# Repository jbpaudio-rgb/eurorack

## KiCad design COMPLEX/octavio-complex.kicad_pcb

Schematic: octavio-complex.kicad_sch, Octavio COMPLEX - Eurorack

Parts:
C1, C2: 10u 25V; C_1206_3216Metric; MPN X5R/X7R 1206
C3, C8: 100p; C_0603_1608Metric
C4, C9: 10n C0G; C_1206_3216Metric; MPN 10 nF C0G/NP0 1206 (condensateur de tim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
C5, C10: 220p; C_0603_1608Metric
C6, C16: 47p; C_0603_1608Metric
C7, C17, C18, C19, C20, C21, C22, C23, C24, C25, C26, C27, C28, C29, C30, C31, C32, C33, C34, C35, C36, C37, C38, C39, C40, C41, C42, C43, C44, C45, C46: 100n; C_0603_1608Metric
C11, C12, C13, C14, C15: 22p; C_0603_1608Metric
C47, C48: 330p; C_0603_1608Metric
D1, D2: SS14; D_SMA; MPN SS14 (40 V 1 A Schottky)
D3, D4, D5, D6, D7, D8, D9, D10, D11, D12, D13, D14, D15, D16, D17, D18, D19, D20: 1N4148W; D_SOD-123; MPN 1N4148W
J1: Eurorack 2x5; IDC-Header_2x05_P2.54mm_Vertical; MPN Shrouded header 2x5 2.54 mm
J2, J9: 1V/OCT; Jack_3.5mm_Thonkiconn_PJ398SM; MPN QingPu WQP-PJ301M-12 (Thonkiconn)
J3, J10: CV; Jack_3.5mm_Thonkiconn_PJ398SM; MPN QingPu WQP-PJ301M-12 (Thonkiconn)
J4, J11: FM; Jack_3.5mm_Thonkiconn_PJ398SM; MPN QingPu WQP-PJ301M-12 (Thonkiconn)
J5: TRI; Jack_3.5mm_Thonkiconn_PJ398SM; MPN QingPu WQP-PJ301M-12 (Thonkiconn)
J6: SIGNAL; Jack_3.5mm_Thonkiconn_PJ398SM; MPN QingPu WQP-PJ301M-12 (Thonkiconn)
J7: INDEX CV; Jack_3.5mm_Thonkiconn_PJ398SM; MPN QingPu WQP-PJ301M-12 (Thonkiconn)
J8: PHASE LOCK; Jack_3.5mm_Thonkiconn_PJ398SM; MPN QingPu WQP-PJ301M-12 (Thonkiconn)
J12: SINE; Jack_3.5mm_Thonkiconn_PJ398SM; MPN QingPu WQP-PJ301M-12 (Thonkiconn)
J13: SQUARE; Jack_3.5mm_Thonkiconn_PJ398SM; MPN QingPu WQP-PJ301M-12 (Thonkiconn)
J14: SYMMETRY CV; Jack_3.5mm_Thonkiconn_PJ398SM; MPN QingPu WQP-PJ301M-12 (Thonkiconn)
J15: TIMBRE CV; Jack_3.5mm_Thonkiconn_PJ398SM; MPN QingPu WQP-PJ301M-12 (Thonkiconn)
J16: ORDER CV; Jack_3.5mm_Thonkiconn_PJ398SM; MPN QingPu WQP-PJ301M-12 (Thonkiconn)
J17: FINAL; Jack_3.5mm_Thonkiconn_PJ398SM; MPN QingPu WQP-PJ301M-12 (Thonkiconn)
Q1, Q3, Q5: BC847DS; SOT-457; MPN BC847DS,115 (Nexperia, paire double)
Q2, Q4: MMBFJ112; SOT-23; MPN MMBFJ112 (JFET N, D-S-G)
R1, R51: 14k; R_0603_1608Metric
R2, R3, R4, R8, R22, R25, R26, R28, R31, R32, R33, R40, R41, R52, R53, R54, R70, R73, R74, R76, R79, R80, R98, R103, R104, R106, R111, R112, R121, R122, R123, R124, R126, R127, R129, R130, R132, R133, R135, R141, R143, R144, R146, R147, R149, R153, R154, R155, R163, R164, R165, R173, R174, R175, R193, R196: 10k; R_0603_1608Metric
R5, R6, R55, R56: 5k36; R_0603_1608Metric
R7: 7k15; R_0603_1608Metric
R9, R10, R12, R14, R15, R16, R36, R37, R38, R39, R49, R57, R58, R60, R62, R63, R95, R96, R97, R101, R102, R109, R110, R119, R120: 100k; R_0603_1608Metric
R11: 100k; R_0603_1608Metric; MPN 100k 0,1 % 25 ppm
R13, R61, R87, R194, R197: 1M; R_0603_1608Metric
R17, R65: 1k TC; R_0603_1608Metric; MPN 1k +3300 ppm/K (thermistance de compens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
R18, R66, R82, R83: 680; R_0603_1608Metric
R19, R67: 549k; R_0603_1608Metric
R20, R34, R35, R68, R92, R93, R192: 1k; R_0603_1608Metric
R21, R50, R69: 22k; R_0603_1608Metric
R23, R27, R71, R75, R99, R105, R136, R150, R183, R185: 20k; R_0603_1608Metric
R24, R72, R107, R145, R148, R184: 48k7; R_0603_1608Metric
R29, R77: 40k2; R_0603_1608Metric
R30, R78: 95k3; R_0603_1608Metric
R42, R47, R48, R81, R85, R86, R113, R156, R161, R162, R166, R171, R172, R176, R181, R182, R186, R191: 47k; R_0603_1608Metric
R43, R44, R114, R115, R157, R158, R167, R168, R177, R178, R187, R188: 100; R_0603_1608Metric
R45, R159, R169, R179: 19k1; R_0603_1608Metric
R46, R160, R170, R180: 2k15; R_0603_1608Metric
R59: 100k; R_0603_1608Metric; MPN 100k 0,1 % 25 ppm (précision 1 V/oct)
R64, R118: 200k; R_0603_1608Metric
R84: 113k; R_0603_1608Metric
R88, R90: 470k; R_0603_1608Metric
R89, R91: 560k; R_0603_1608Metric
R94, R100, R108: 2k; R_0603_1608Metric
R116: 27k; R_0603_1608Metric
R117: 3k; R_0603_1608Metric
R125, R128: 46k4; R_0603_1608Metric
R131, R134: 15k4; R_0603_1608Metric
R137, R138, R139, R140, R151, R152: 4k99; R_0603_1608Metric
R142: 6k98; R_0603_1608Metric
R189: 9k53; R_0603_1608Metric
R190: 1k07; R_0603_1608Metric
R195, R198: 4k7; R_0603_1608Metric
RV1, RV2, RV3, RV4, RV7, RV8, RV9, RV10, RV11, RV12, RV16, RV17, RV18, RV19: 10k B; Pot_Alpha_9mm_Vertical; MPN POT-R09V-10K (9 mm vertical, B10k)
RV5, RV13: 500; Trim_SMD_Bourns_3314J; MPN Bourns 3314J-1-501E (réglage V/OCT)
RV6, RV14: 1k; Trim_SMD_Bourns_3314J; MPN Bourns 3314J-1-102E (réglage HF)
RV15: 1k; Trim_SMD_Bourns_3314J; MPN Bourns 3314J-1-102E (symétrie du sinus)
SW1: AUDIO / LFO; Toggle_SPDT_Dailywell_2MS1; MPN C&K T101MH9ABE (SPDT ON-ON)
SW2: TRI / SQR / SAW; Toggle_SPDT_Dailywell_2MS1; MPN SPDT ON-OFF-ON (ex. C&K T103MH9ABE) : c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
SW3: AMPL ON / OFF; Toggle_SPDT_Dailywell_2MS1; MPN C&K T101MH9ABE (SPDT ON-ON)
SW4: PITCH ON / OFF; Toggle_SPDT_Dailywell_2MS1; MPN C&K T101MH9ABE (SPDT ON-ON)
SW5: TIMBRE ON / OFF; Toggle_SPDT_Dailywell_2MS1; MPN C&K T101MH9ABE (SPDT ON-ON)
U1, U2, U3, U4, U5, U6, U7, U8, U9, U10, U11, U12: TL074; SOIC-14_3.9x8.7mm_P1.27mm; MPN TL074CDR
U13, U14, U15: LM13700; SOIC-16_3.9x9.9mm_P1.27mm; MPN LM13700MX/NOPB

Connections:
+12V: C1.1, C17.1, C19.1, C21.1, C23.1, C25.1, C27.1, C29.1, C31.1, C33.1, C35.1, C37.1, C39.1, C41.1, C43.1, C45.1, D1.1 (K), R1.1, R3.1, R5.1, R19.1, R30.1, R51.1, R53.1, R55.1, R67.1, R78.1, R85.1, R86.1, R94.1, R100.1, R108.1, R128.1, R134.1, R148.1, RV15.3, U1.4 (V+), U2.4 (V+), U3.4 (V+), U4.4 (V+), U5.4 (V+), U6.4 (V+), U7.4 (V+), U8.4 (V+), U9.4 (V+), U10.4 (V+), U11.4 (V+), U12.4 (V+), U13.11 (V+), U14.11 (V+), U15.11 (V+)
+12V_IN: D1.2 (A), J1.9, J1.10
-12V: C2.2, C18.2, C20.2, C22.2, C24.2, C26.2, C28.2, C30.2, C32.2, C34.2, C36.2, C38.2, C40.2, C42.2, C44.2, C46.2, D2.2 (A), R4.2, R6.2, R7.1, R21.2, R24.1, R46.2, R54.2, R56.2, R69.2, R72.1, R84.2, R107.1, R117.2, R125.1, R131.1, R145.1, R160.2, R170.2, R180.2, R184.1, R190.2, RV15.1, U1.11 (V-), U2.11 (V-), U3.11 (V-), U4.11 (V-), U5.11 (V-), U6.11 (V-), U7.11 (V-), U8.11 (V-), U9.11 (V-), U10.11 (V-), U11.11 (V-), U12.11 (V-), U13.6 (V-), U14.6 (V-), U15.6 (V-)
-12V_IN: D2.1 (K), J1.1, J1.2
AMN: R183.2, R184.2, R185.1, U12.6 (-B)
AMV: R185.2, R189.1, U12.7 (OB)
COMA: R183.1, SW3.2 (COM)
COMP: R64.1, SW4.2 (COM)
COMT: R97.1, SW5.2 (COM)
C_CMPP: C48.2, R196.2, R197.2, U5.5 (+B)
C_EN: Q3.1 (E1), Q3.4 (E2), R68.2
C_FB1: R65.2, RV13.1
C_FB2: R66.1, RV13.2 (W), RV13.3
C_GATE: C10.2, Q4.3 (C), R69.1, R198.2
C_GX: C10.1, D20.1 (K), R198.1
C_HFC: C9.2, Q4.1 (B), RV14.1
C_HWA: D5.1 (K), D6.2 (A), U5.14 (OD)
C_HWN: D6.1 (K), R73.2, R74.1, U5.13 (-D)
C_HWO: D5.2 (A), R74.2, R76.1
C_INTN: C9.1, Q3.3 (C2), Q4.2 (E), U5.2 (-A)
C_QRC: C8.2, Q3.6 (C1), R67.2, U4.13 (-D)
C_RAMP: R70.1, R196.1, RV14.2 (W), RV14.3, U5.1 (OA)
C_REF: R50.2, R51.2, R52.1, U5.6 (-B)
C_RSTQ: C48.1, D20.2 (A), R197.1, U5.7 (OB)
C_SAWN: R70.2, R71.1, R72.2, U5.9 (-C)
C_SAWO: R71.2, R73.1, R75.1, R154.1, R161.1, U5.8 (OC), U6.5 (+B)
C_SB1: Q5.2 (B1), R81.2, R82.1
C_SB2: Q5.5 (B2), R83.1, R87.2
C_SC1: Q5.6 (C1), R85.2, R88.1
C_SC2: Q5.3 (C2), R86.2, R90.1
C_SE: Q5.1 (E1), Q5.4 (E2), R84.1
C_SINN: R88.2, R89.1, U6.9 (-C)
C_SINO: R89.2, R92.1, R113.1, R118.1, R141.1, R164.1, R171.1, U6.8 (OC)
C_SINP: R90.2, R91.1, U6.10 (+C)
C_SINT: R87.1, RV15.2 (W)
C_SN: R59.2, R60.2, R61.2, R62.2, R63.2, R64.2, R65.1, U4.9 (-C)
C_SQC: R79.1, U6.7 (OB)
C_SQO: R79.2, R80.1, U6.12 (+D)
C_TRIO: R77.2, R81.1, U6.1 (OA)
C_TRN: R75.2, R76.2, R77.1, R78.2, U6.2 (-A)
C_VD: C8.1, R68.1, U4.14 (OD)
C_VREFB: Q3.2 (B1), R66.2, U4.8 (OC)
FINALJ: J17.T, R192.2
FINALO: C16.2, R191.2, R192.1, U12.8 (OC)
FOLDO: C12.2, R136.2, R174.1, R181.1, U9.8 (OC)
FS: C12.1, R135.2, R136.1, R137.2, R138.2, R139.2, R140.2, U9.9 (-C)
GND: C1.2, C2.1, C17.2, C18.1, C19.2, C20.1, C21.2, C22.1, C23.2, C24.1, C25.2, C26.1, C27.2, C28.1, C29.2, C30.1, C31.2, C32.1, C33.2, C34.1, C35.2, C36.1, C37.2, C38.1, C39.2, C40.1, C41.2, C42.1, C43.2, C44.1, C45.2, C46.1, J1.3, J1.4, J1.5, J1.6, J1.7, J1.8, J2.S, J2.TN, J3.S, J3.TN, J4.S, J4.TN, J5.S, J6.S, J7.S, J7.TN, J8.S, J8.TN, J9.S, J9.TN, J10.S, J10.TN, J11.S, J11.TN, J12.S, J13.S, J14.S, J14.TN, J15.S, J15.TN, J16.S, J16.TN, J17.S, Q1.5 (B2), Q3.5 (B2), R2.2, R8.2, R32.2, R39.2, R40.2, R43.2, R44.2, R49.2, R52.2, R80.2, R82.2, R83.2, R91.2, R98.2, R103.2, R111.2, R114.2, R115.2, R157.2, R158.2, R167.2, R168.2, R177.2, R178.2, R187.2, R188.2, RV4.1 (CCW), RV8.1 (CCW), RV12.1 (CCW), RV16.1 (CCW), RV17.1 (CCW), RV18.1 (CCW), RV19.1 (CCW), SW1.1, SW3.3, SW4.3, SW5.3, U1.3 (+A), U1.5 (+B), U1.10 (+C), U1.12 (+D), U2.5 (+B), U2.10 (+C), U2.12 (+D), U3.2 (-A), U3.10 (+C), U4.3 (+A), U4.5 (+B), U4.10 (+C), U4.12 (+D), U5.3 (+A), U5.10 (+C), U5.12 (+D), U6.3 (+A), U6.6 (-B), U7.10 (+C), U8.3 (+A), U8.5 (+B), U8.10 (+C), U8.12 (+D), U9.3 (+A), U9.5 (+B), U9.10 (+C), U9.12 (+D), U10.3 (+A), U10.5 (+B), U10.10 (+C), U10.12 (+D), U11.3 (+A), U11.5 (+B), U11.10 (+C), U11.12 (+D), U12.3 (+A), U12.5 (+B), U12.10 (+C), U12.12 (+D)
IXCN: R40.1, R41.2, U3.13 (-D)
IXCP: R38.2, R39.1, U3.12 (+D)
IXCV: R41.1, R45.1, U3.14 (OD)
IXCVJ: J7.T, R38.1
IX_W: R47.1, RV7.2 (W)
LFOREF: R7.2, R8.1, SW1.3
MCVIN: R9.2, R10.1, U1.2 (-A)
MCVINV: R10.2, RV3.1 (CCW), U1.1 (OA)
MCVJ: J3.T, R9.1, RV3.3 (CW)
MCV_W: R14.1, RV3.2 (W)
MFB: R6.1, RV2.1 (CCW)
MFMJ: J4.T, RV4.3 (CW)
MFM_W: R15.1, RV4.2 (W)
MFN_W: R13.1, RV2.2 (W)
MFT: R5.2, RV2.3 (CW)
MF_W: R12.1, RV1.2 (W)
MIN: C6.2, R48.2, SW3.1, SW4.1, SW5.1, U4.1 (OA)
MISUM: C6.1, R47.2, R48.1, U4.2 (-A), U13.5 (OUT1)
MKB: R4.1, RV1.1 (CCW)
MKT: R3.2, RV1.3 (CW)
MO: R150.2, R153.1, U10.8 (OC)
MODW: R34.1, R36.1, R42.1, RV7.3 (CW), U3.6 (-B), U3.7 (OB)
MS: R149.2, R150.1, R151.2, R152.2, U10.9 (-C)
MSIGJ: J6.T, R34.2
MTRIJ: J5.T, R35.2
MVOJ: J2.T, R11.1
MWIIN: R36.2, R37.1, U3.9 (-C)
MWIINV: R37.2, RV7.1 (CCW), U3.8 (OC)
MWSEL: R33.2, SW2.2 (COM), U3.5 (+B)
M_CMPP: C47.2, R193.2, R194.2, U2.3 (+A)
M_EN: Q1.1 (E1), Q1.4 (E2), R20.2
M_FB1: R17.2, RV5.1
M_FB2: R18.1, RV5.2 (W), RV5.3
M_GATE: C5.2, Q2.3 (C), R21.1, R195.2
M_GX: C5.1, D19.1 (K), R195.1
M_HFC: C4.2, Q2.1 (B), RV6.1
M_HWA: D3.1 (K), D4.2 (A), U2.8 (OC)
M_HWN: D4.1 (K), R25.2, R26.1, U2.9 (-C)
M_HWO: D3.2 (A), R26.2, R28.1
M_INTN: C4.1, Q1.3 (C2), Q2.2 (E), U1.13 (-D)
M_QRC: C3.2, Q1.6 (C1), R19.2, U1.9 (-C)
M_RAMP: R22.1, R193.1, RV6.2 (W), RV6.3, U1.14 (OD)
M_RSTQ: C47.1, D19.2 (A), R194.1, U2.1 (OA)
M_SAWN: R22.2, R23.1, R24.2, U2.6 (-B)
M_SAWO: R23.2, R25.1, R27.1, SW2.3, U2.7 (OB), U3.3 (+A)
M_SN: R11.2, R12.2, R13.2, R14.2, R15.2, R16.2, R17.1, U1.6 (-B)
M_SQC: R31.1, U3.1 (OA)
M_SQO: R31.2, R32.1, R33.1
M_TRIO: R29.2, R35.1, SW2.1, U2.14 (OD)
M_TRN: R27.2, R28.2, R29.1, R30.2, U2.13 (-D)
M_VD: C3.1, R20.1, U1.8 (OC)
M_VREFB: Q1.2 (B1), R18.2, U1.7 (OB)
O00I: R45.2, R46.1, U13.1 (IABC1)
O00N: R44.1, U13.4 (-IN1)
O00P: R42.2, R43.1, U13.3 (+IN1)
O01I: R116.2, R117.1, U13.16 (IABC2)
O01N: R115.1, U13.13 (-IN2)
O01P: R113.2, R114.1, U13.14 (+IN2)
O10I: R159.2, R160.1, U14.1 (IABC1)
O10N: R158.1, U14.4 (-IN1)
O10P: R156.2, R157.1, U14.3 (+IN1)
O11I: R169.2, R170.1, U14.16 (IABC2)
O11N: R168.1, U14.13 (-IN2)
O11P: R166.2, R167.1, U14.14 (+IN2)
O20I: R179.2, R180.1, U15.1 (IABC1)
O20N: R178.1, U15.4 (-IN1)
O20P: R176.2, R177.1, U15.3 (+IN1)
O21I: R189.2, R190.1, U15.16 (IABC2)
O21N: R188.1, U15.13 (-IN2)
O21P: R186.2, R187.1, U15.14 (+IN2)
ORCVJ: J16.T, R110.1
ORT: R108.2, RV19.3 (CW)
ORV: R112.1, R179.1, U7.14 (OD)
ORV_N: R111.1, R112.2, U7.13 (-D)
ORV_P: R109.2, R110.2, U7.12 (+D)
OR_W: R109.1, RV19.2 (W)
OSUM: C16.1, R191.1, U12.9 (-C), U15.12 (OUT2)
PCVIN: R57.2, R58.1, U4.6 (-B)
PCVINV: R58.2, RV11.1 (CCW), U4.7 (OB)
PCVJ: J10.T, R57.1, RV11.3 (CW)
PCV_W: R62.1, RV11.2 (W)
PFB: R56.1, RV10.1 (CCW)
PFMJ: J11.T, RV12.3 (CW)
PFM_W: R63.1, RV12.2 (W)
PFN_W: R61.1, RV10.2 (W)
PFT: R55.2, RV10.3 (CW)
PF_W: R60.1, RV9.2 (W)
PKB: R54.1, RV9.1 (CCW)
PKT: R53.2, RV9.3 (CW)
PLAC: C7.2, R49.1, RV8.3 (CW)
PLJ: C7.1, J8.T
PL_W: R50.1, RV8.2 (W)
PVOJ: J9.T, R59.1
REF5: R1.2, R2.1, U2.2 (-A)
RNGS: R16.1, SW1.2 (COM)
SDN: R105.2, R106.1, R107.2, U7.9 (-C)
SINEJ: J12.T, R92.2
SQB: R93.1, U6.13 (-D), U6.14 (OD)
SQJ: J13.T, R93.2
SYCVJ: J14.T, R102.1
SYDC: R106.2, R119.1, U7.8 (OC)
SYT: R100.2, RV18.3 (CW)
SYV: R104.1, R105.1, R159.1, U7.7 (OB)
SYV_N: R103.1, R104.2, U7.6 (-B)
SYV_P: R101.2, R102.2, U7.5 (+B)
SY_W: R101.1, RV18.2 (W)
TBN: R98.1, R99.2, U7.2 (-A)
TBP: R95.2, R96.2, R97.2, U7.3 (+A)
TBT: R94.2, RV16.3 (CW)
TBV: R99.1, R116.1, R169.1, U7.1 (OA)
TB_W: R95.1, RV16.2 (W)
TCVJ: J15.T, RV17.3 (CW)
TCV_W: R96.1, RV17.2 (W)
UNUSED113: U12.13 (-D), U12.14 (OD)
X: C11.2, R120.2, R121.1, R123.1, R126.1, R135.1, U8.1 (OA)
XIN: R121.2, R122.1, U8.6 (-B)
XM: R142.2, R143.1, R146.1, R149.1, U9.14 (OD)
XMN: R141.2, R142.1, U9.13 (-D)
XN: R122.2, R129.1, R132.1, U8.7 (OB)
XS: C13.2, R162.2, R163.1, U11.1 (OA)
XSUM: C11.1, R118.2, R119.2, R120.1, U8.2 (-A), U13.12 (OUT2)
XS_D: R155.2, R156.1, U10.14 (OD)
XS_DN: R153.2, R154.2, R155.1, U10.13 (-D)
XS_S: C13.1, R161.2, R162.1, U11.2 (-A), U14.5 (OUT1)
Y1N: D10.1 (K), R127.1, R138.1
Y1N_N: D9.2 (A), R126.2, R127.2, R128.2, U8.13 (-D)
Y1N_O: D9.1 (K), D10.2 (A), U8.14 (OD)
Y1P: D8.2 (A), R124.1, R137.1
Y1P_N: D7.1 (K), R123.2, R124.2, R125.2, U8.9 (-C)
Y1P_O: D7.2 (A), D8.1 (K), U8.8 (OC)
Y2N: D14.1 (K), R133.1, R140.1
Y2N_N: D13.2 (A), R132.2, R133.2, R134.2, U9.6 (-B)
Y2N_O: D13.1 (K), D14.2 (A), U9.7 (OB)
Y2P: D12.2 (A), R130.1, R139.1
Y2P_N: D11.1 (K), R129.2, R130.2, R131.2, U9.2 (-A)
Y2P_O: D11.2 (A), D12.1 (K), U9.1 (OA)
YMN: D18.1 (K), R147.1, R152.1
YMN_N: D17.2 (A), R146.2, R147.2, R148.2, U10.6 (-B)
YMN_O: D17.1 (K), D18.2 (A), U10.7 (OB)
YMP: D16.2 (A), R144.1, R151.1
YMP_N: D15.1 (K), R143.2, R144.2, R145.2, U10.2 (-A)
YMP_O: D15.2 (A), D16.1 (K), U10.1 (OA)
YS: C14.2, R172.2, R173.1, U11.8 (OC)
YS_D: R165.2, R166.1, U11.7 (OB)
YS_DN: R163.2, R164.2, R165.1, U11.6 (-B)
YS_S: C14.1, R171.2, R172.1, U11.9 (-C), U14.12 (OUT2)
ZS: C15.2, R182.2, R186.1, U12.1 (OA)
ZS_D: R175.2, R176.1, U11.14 (OD)
ZS_DN: R173.2, R174.2, R175.1, U11.13 (-D)
ZS_S: C15.1, R181.2, R182.1, U12.2 (-A), U15.5 (OUT1)

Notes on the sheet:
POWER (Eurorack 10 pins)
MOD OSC : FREQ, FINE, RANGE, CV, FM
MODULATION OSC CORE (expo, saw, triangle, square)
MOD OSC : WAVE, OUTPUTS
MOD INDEX (attenuverter + CV OTA), AMPL / PITCH / TIMBRE
PHASE LOCK
PRINCIPAL OSC : FREQ, FINE, CV, FM
COMPLEX OSC CORE (expo, saw, triangle, square)
SINE SHAPER, SINE / SQUARE OUTPUTS
HARMONICS : TIMBRE / SYMMETRY / ORDER controls
HARMONICS : WAVE FOLDER (TIMBRE drive, SYMMETRY DC)
HARMONICS : M SHAPER
HARMONICS : SYMMETRY / TIMBRE / ORDER CROSSFADES
AM + FINAL OUTPUT
JACKS
ICs + DECOUPLING
NOTES
- Architecture inspiree du Buchla 259 (circuit original Octavio) : osc. de modulation, section MOD, osc. principal, HARMONICS.
- Deux coeurs dent de scie facon 921 ; 0 V = 440 Hz (R 549k) ; FREQUENCY +/-4 V = 8 octaves (27 Hz a 7 kHz), FINE +/- une quinte, LFO = -7 octaves.
- MOD INDEX : attenuverter sur le signal de modulation + OTA pour INDEX CV ; AMPL / PITCH / TIMBRE (haut = ON) envoient MIN vers l'AM, le convertisseur expo (200k) et la commande de timbre.
- PHASE LOCK : entree couplee en alternatif injectee dans la reference de remise a zero du coeur principal (verrouillage par injection).
- HARMONICS : replieur (OTA x1..x4 + seuils 2,6 V / 7,8 V, DC de SYMMETRY), forme M (repli doux a 2,5 V), dent de scie du coeur.
- X = SAW -> M (SYMMETRY), Y = SINE -> X (TIMBRE), FINAL = REPLIE -> Y (ORDER), puis AM (OTA).
- -12V = bande rouge du cable.

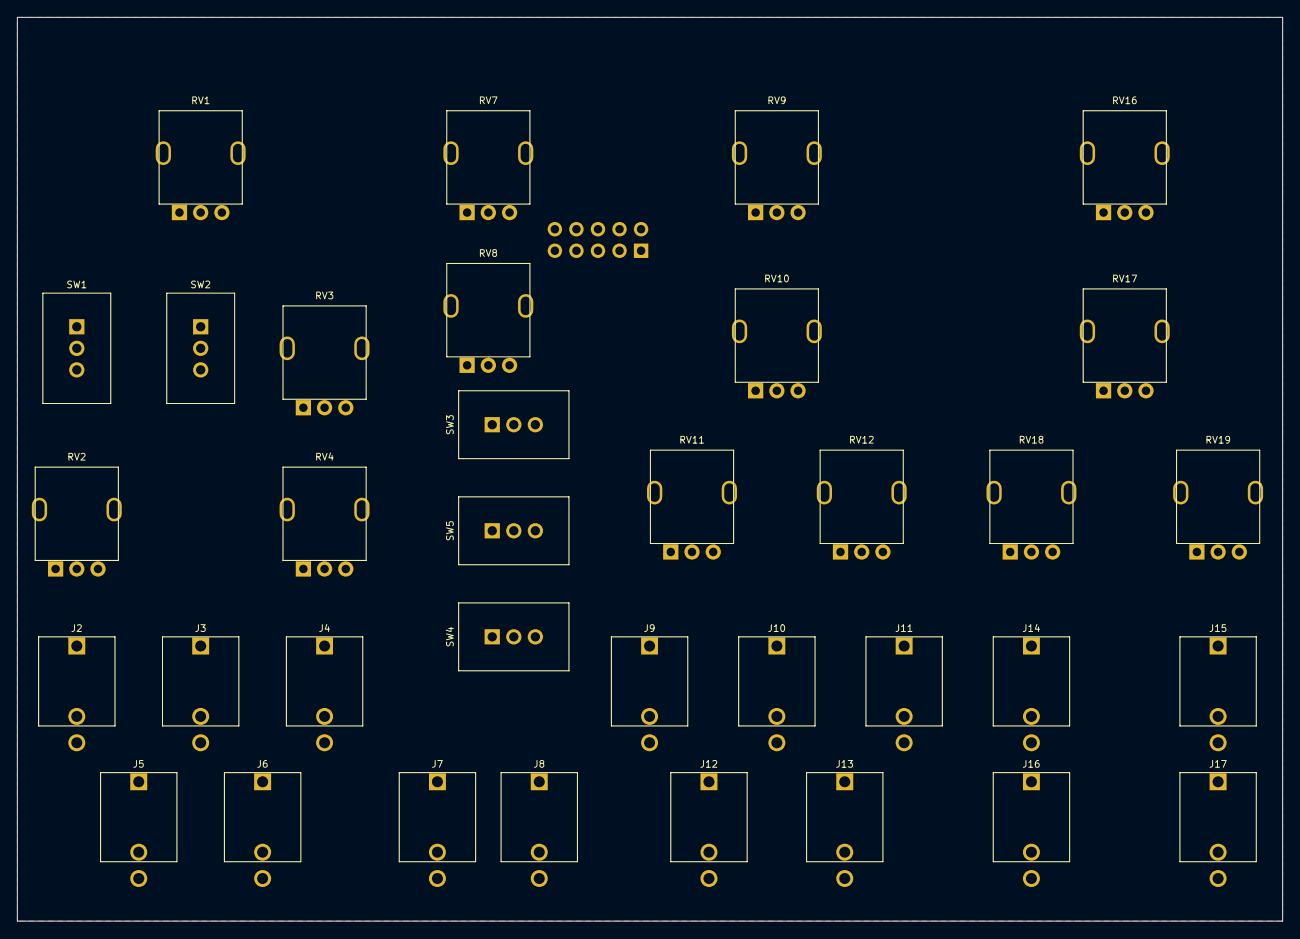
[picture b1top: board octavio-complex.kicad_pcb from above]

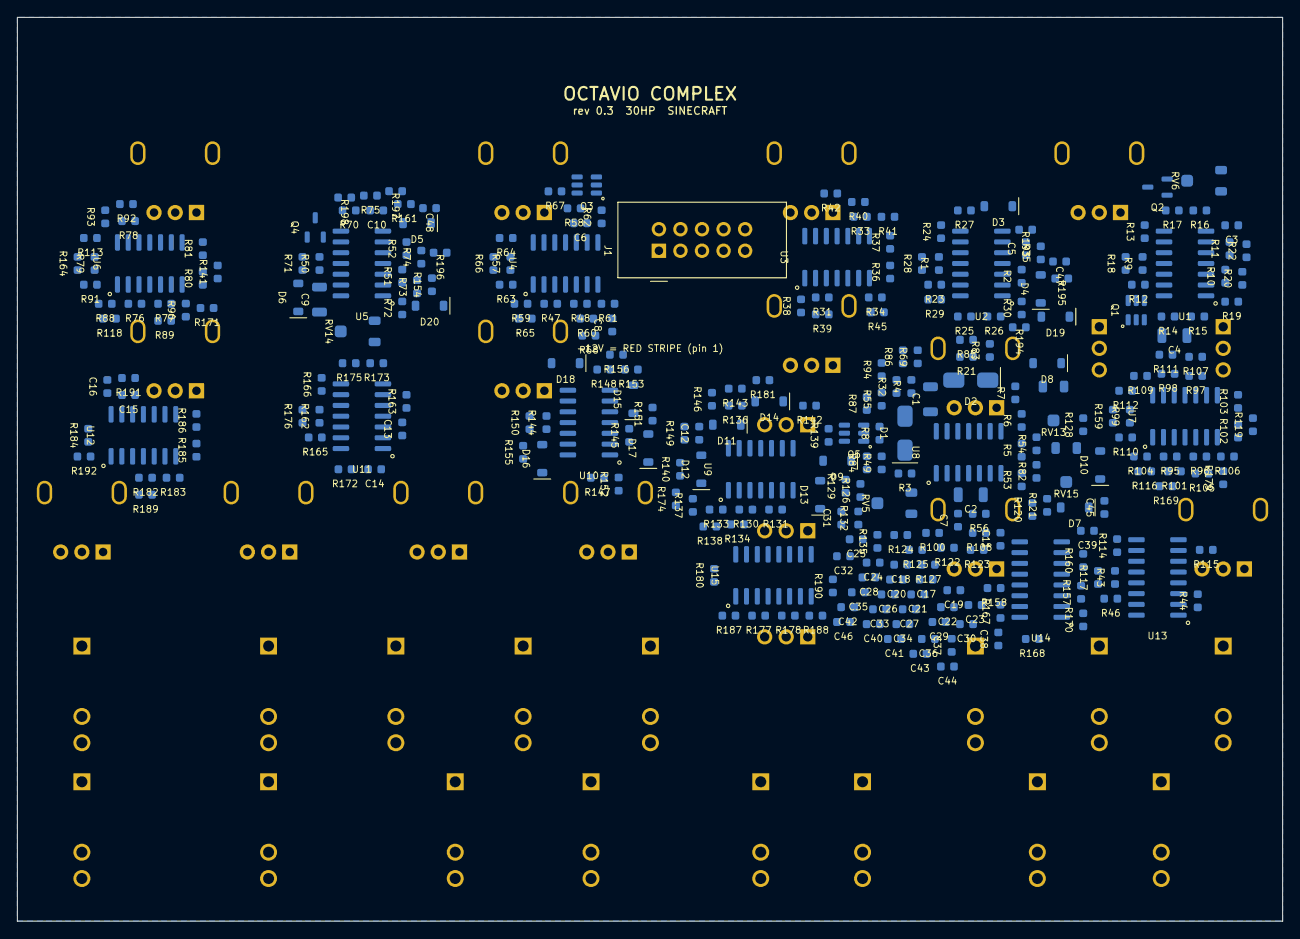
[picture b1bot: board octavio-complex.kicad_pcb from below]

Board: 2 copper layers, 149.1 x 106.5 mm, 327 parts (292 on the bottom side), 197 nets, no tracks yet.

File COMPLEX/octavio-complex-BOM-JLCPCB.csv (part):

Comment,Designator,Footprint,LCSC Part #,Notes
10u 25V X5R/X7R 1206,"C1,C2",C_1206_3216Metric,,X5R/X7R 1206 - SMT bottom - laisser JLC choisir (Basic de preference)
22p,"C11,C12,C13,C14,C15",C_0603_1608Metric,,SMT bottom - laisser JLC choisir (Basic de preference)
100p,"C3,C8",C_0603_1608Metric,,SMT bottom - laisser JLC choisir (Basic de preference)
10n C0G 10 nF C0G/NP0 1206,"C4,C9",C_1206_3216Metric,,10 nF C0G/NP0 1206 (condensateur de timing) - SMT bottom - laisser JLC choisir (Basic de preference)
220p,"C5,C10",C_0603_1608Metric,,SMT bottom - laisser JLC choisir (Basic de preference)
47p,"C6,C16",C_0603_1608Metric,,SMT bottom - laisser JLC choisir (Basic de preference)
100n,"C7,C17,C18,C19,C20,C21,C22,C23,C24,C25,C26,C27,C28,C29,C30,C31,C32,C33,C34,C35,C36,C37,C38,C39,C40,C41,C42,C43,C44,C45,C46",C_0603_1608Metric,,SMT bottom - laisser JLC choisir (Basic de preference)
SS14,"D1,D2",D_SMA,,SS14 (40 V 1 A Schottky) - SMT bottom - laisser JLC choisir (Basic de preference)
1N4148W,"D3,D4,D5,D6,D7,D8,D9,D10,D11,D12,D13,D14,D15,D16,D17,D18,D19,D20",D_SOD-123,,1N4148W - SMT bottom - laisser JLC choisir (Basic de preference)
Eurorack 2x5,J1,IDC-Header_2x05_P2.54mm_Vertical,,Shrouded header 2x5 2.54 mm - THT (wave soldering) - laisser JLC choisir (Basic de preference)
SINE,J12,Jack_3.5mm_Thonkiconn_PJ398SM,C9900080080,QingPu WQP-PJ301M-12 (Thonkiconn) - THT (wave soldering)
SQUARE,J13,Jack_3.5mm_Thonkiconn_PJ398SM,C9900080080,QingPu WQP-PJ301M-12 (Thonkiconn) - THT (wave soldering)
SYMMETRY CV,J14,Jack_3.5mm_Thonkiconn_PJ398SM,C9900080080,QingPu WQP-PJ301M-12 (Thonkiconn) - THT (wave soldering)
TIMBRE CV,J15,Jack_3.5mm_Thonkiconn_PJ398SM,C9900080080,QingPu WQP-PJ301M-12 (Thonkiconn) - THT (wave soldering)
ORDER CV,J16,Jack_3.5mm_Thonkiconn_PJ398SM,C9900080080,QingPu WQP-PJ301M-12 (Thonkiconn) - THT (wave soldering)
FINAL,J17,Jack_3.5mm_Thonkiconn_PJ398SM,C9900080080,QingPu WQP-PJ301M-12 (Thonkiconn) - THT (wave soldering)
1V/OCT,"J2,J9",Jack_3.5mm_Thonkiconn_PJ398SM,C9900080080,QingPu WQP-PJ301M-12 (Thonkiconn) - THT (wave soldering)
CV,"J3,J10",Jack_3.5mm_Thonkiconn_PJ398SM,C9900080080,QingPu WQP-PJ301M-12 (Thonkiconn) - THT (wave soldering)
FM,"J4,J11",Jack_3.5mm_Thonkiconn_PJ398SM,C9900080080,QingPu WQP-PJ301M-12 (Thonkiconn) - THT (wave soldering)
TRI,J5,Jack_3.5mm_Thonkiconn_PJ398SM,C9900080080,QingPu WQP-PJ301M-12 (Thonkiconn) - THT (wave soldering)
SIGNAL,J6,Jack_3.5mm_Thonkiconn_PJ398SM,C9900080080,QingPu WQP-PJ301M-12 (Thonkiconn) - THT (wave soldering)
INDEX CV,J7,Jack_3.5mm_Thonkiconn_PJ398SM,C9900080080,QingPu WQP-PJ301M-12 (Thonkiconn) - THT (wave soldering)
PHASE LOCK,J8,Jack_3.5mm_Thonkiconn_PJ398SM,C9900080080,QingPu WQP-PJ301M-12 (Thonkiconn) - THT (wave soldering)
"BC847DS,115","Q1,Q3,Q5",SOT-457,C549489,"BC847DS,115 (Nexperia, paire double) - SMT bottom"
MMBFJ112,"Q2,Q4",SOT-23,,"MMBFJ112 (JFET N, D-S-G) - SMT bottom - laisser JLC choisir (Basic de preference)"
14k 1% 0805,"R1,R51",R_0603_1608Metric,,SMT bottom - laisser JLC choisir (Basic de preference)
100k 1% 0805,R11,R_0603_1608Metric,,"100k 0,1 % 25 ppm - SMT bottom - laisser JLC choisir (Basic de preference)"
27k 1% 0805,R116,R_0603_1608Metric,,SMT bottom - laisser JLC choisir (Basic de preference)
3k 1% 0805,R117,R_0603_1608Metric,,SMT bottom - laisser JLC choisir (Basic de preference)
46k4 1% 0805,"R125,R128",R_0603_1608Metric,,SMT bottom - laisser JLC choisir (Basic de preference)
1M 1% 0805,"R13,R61,R87,R194,R197",R_0603_1608Metric,,SMT bottom - laisser JLC choisir (Basic de preference)
15k4 1% 0805,"R131,R134",R_0603_1608Metric,,SMT bottom - laisser JLC choisir (Basic de preference)
4k99 1% 0805,"R137,R138,R139,R140,R151,R152",R_0603_1608Metric,,SMT bottom - laisser JLC choisir (Basic de preference)
6k98 1% 0805,R142,R_0603_1608Metric,,SMT bottom - laisser JLC choisir (Basic de preference)
1k TC 1% 0805,"R17,R65",R_0603_1608Metric,,"1k +3300 ppm/K (thermistance de compensation, collée à la paire) - SMT bottom - laisser JLC choisir (Basic de preference)"
680 1% 0805,"R18,R66,R82,R83",R_0603_1608Metric,,SMT bottom - laisser JLC choisir (Basic de preference)
9k53 1% 0805,R189,R_0603_1608Metric,,SMT bottom - laisser JLC choisir (Basic de preference)
549k 1% 0805,"R19,R67",R_0603_1608Metric,,SMT bottom - laisser JLC choisir (Basic de preference)
1k07 1% 0805,R190,R_0603_1608Metric,,SMT bottom - laisser JLC choisir (Basic de preference)
10k 1% 0805,"R2,R3,R4,R8,R22,R25,R26,R28,R31,R32,R33,R40,R41,R52,R53,R54,R70,R73,R74,R76,R79,R80,R98,R103,R104,R106,R111,R112,R121,R122,R123,R124,R126,R127,R129,R130,R132,R133,R135,R141,R143,R144,R146,R147,R149,R153,R154,R155,R163,R164,R165,R173,R174,R175,R193,R196",R_0603_1608Metric,,SMT bottom - laisser JLC choisir (Basic de preference)
1k 1% 0805,"R20,R34,R35,R68,R92,R93,R192",R_0603_1608Metric,,SMT bottom - laisser JLC choisir (Basic de preference)
22k 1% 0805,"R21,R50,R69",R_0603_1608Metric,,SMT bottom - laisser JLC choisir (Basic de preference)
20k 1% 0805,"R23,R27,R71,R75,R99,R105,R136,R150,R183,R185",R_0603_1608Metric,,SMT bottom - laisser JLC choisir (Basic de preference)
48k7 1% 0805,"R24,R72,R107,R145,R148,R184",R_0603_1608Metric,,SMT bottom - laisser JLC choisir (Basic de preference)
40k2 1% 0805,"R29,R77",R_0603_1608Metric,,SMT bottom - laisser JLC choisir (Basic de preference)
95k3 1% 0805,"R30,R78",R_0603_1608Metric,,SMT bottom - laisser JLC choisir (Basic de preference)
47k 1% 0805,"R42,R47,R48,R81,R85,R86,R113,R156,R161,R162,R166,R171,R172,R176,R181,R182,R186,R191",R_0603_1608Metric,,SMT bottom - laisser JLC choisir (Basic de preference)
100 1% 0805,"R43,R44,R114,R115,R157,R158,R167,R168,R177,R178,R187,R188",R_0603_1608Metric,,SMT bottom - laisser JLC choisir (Basic de preference)
19k1 1% 0805,"R45,R159,R169,R179",R_0603_1608Metric,,SMT bottom - laisser JLC choisir (Basic de preference)
2k15 1% 0805,"R46,R160,R170,R180",R_0603_1608Metric,,SMT bottom - laisser JLC choisir (Basic de preference)
5k36 1% 0805,"R5,R6,R55,R56",R_0603_1608Metric,,SMT bottom - laisser JLC choisir (Basic de preference)
100k 1% 0805,R59,R_0603_1608Metric,,"100k 0,1 % 25 ppm (précision 1 V/oct) - SMT bottom - laisser JLC choisir (Basic de preference)"
200k 1% 0805,"R64,R118",R_0603_1608Metric,,SMT bottom - laisser JLC choisir (Basic de preference)
7k15 1% 0805,R7,R_0603_1608Metric,,SMT bottom - laisser JLC choisir (Basic de preference)
113k 1% 0805,R84,R_0603_1608Metric,,SMT bottom - laisser JLC choisir (Basic de preference)
100k 1% 0805,"R9,R10,R12,R14,R15,R16,R36,R37,R38,R39,R49,R57,R58,R60,R62,R63,R95,R96,R97,R101,R102,R109,R110,R119,R120",R_0603_1608Metric,,SMT bottom - laisser JLC choisir (Basic de preference)
2k 1% 0805,"R94,R100,R108",R_0603_1608Metric,,SMT bottom - laisser JLC choisir (Basic de preference)
10k B,"RV1,RV2,RV3,RV4,RV7,RV8,RV9,RV10,RV11,RV12,RV16,RV17,RV18,RV19",Pot_Alpha_9mm_Vertical,,"POT-R09V-10K (9 mm vertical, B10k) - THT (wave soldering) - laisser JLC choisir (Basic de preference)"
1k Bourns 3314J-1-102E,RV15,Trim_SMD_Bourns_3314J,,Bourns 3314J-1-102E (symétrie du sinus) - SMT bottom - laisser JLC choisir (Basic de preference)
500 Bourns 3314J-1-501E,"RV5,RV13",Trim_SMD_Bourns_3314J,,Bourns 3314J-1-501E (réglage V/OCT) - SMT bottom - laisser JLC choisir (Basic de preference)
1k Bourns 3314J-1-102E,"RV6,RV14",Trim_SMD_Bourns_3314J,,Bourns 3314J-1-102E (réglage HF) - SMT bottom - laisser JLC choisir (Basic de preference)
AUDIO / LFO,SW1,Toggle_SPDT_Dailywell_2MS1,,C&K T101MH9ABE (SPDT ON-ON) - THT (wave soldering) - laisser JLC choisir (Basic de preference)
TRI / SQR / SAW,SW2,Toggle_SPDT_Dailywell_2MS1,,SPDT ON-OFF-ON (ex. C&K T103MH9ABE) : centre = carré - THT (wave soldering) - laisser JLC choisir (Basic de preference)
AMPL ON / OFF,SW3,Toggle_SPDT_Dailywell_2MS1,,C&K T101MH9ABE (SPDT ON-ON) - THT (wave soldering) - laisser JLC choisir (Basic de preference)
PITCH ON / OFF,SW4,Toggle_SPDT_Dailywell_2MS1,,C&K T101MH9ABE (SPDT ON-ON) - THT (wave soldering) - laisser JLC choisir (Basic de preference)
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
